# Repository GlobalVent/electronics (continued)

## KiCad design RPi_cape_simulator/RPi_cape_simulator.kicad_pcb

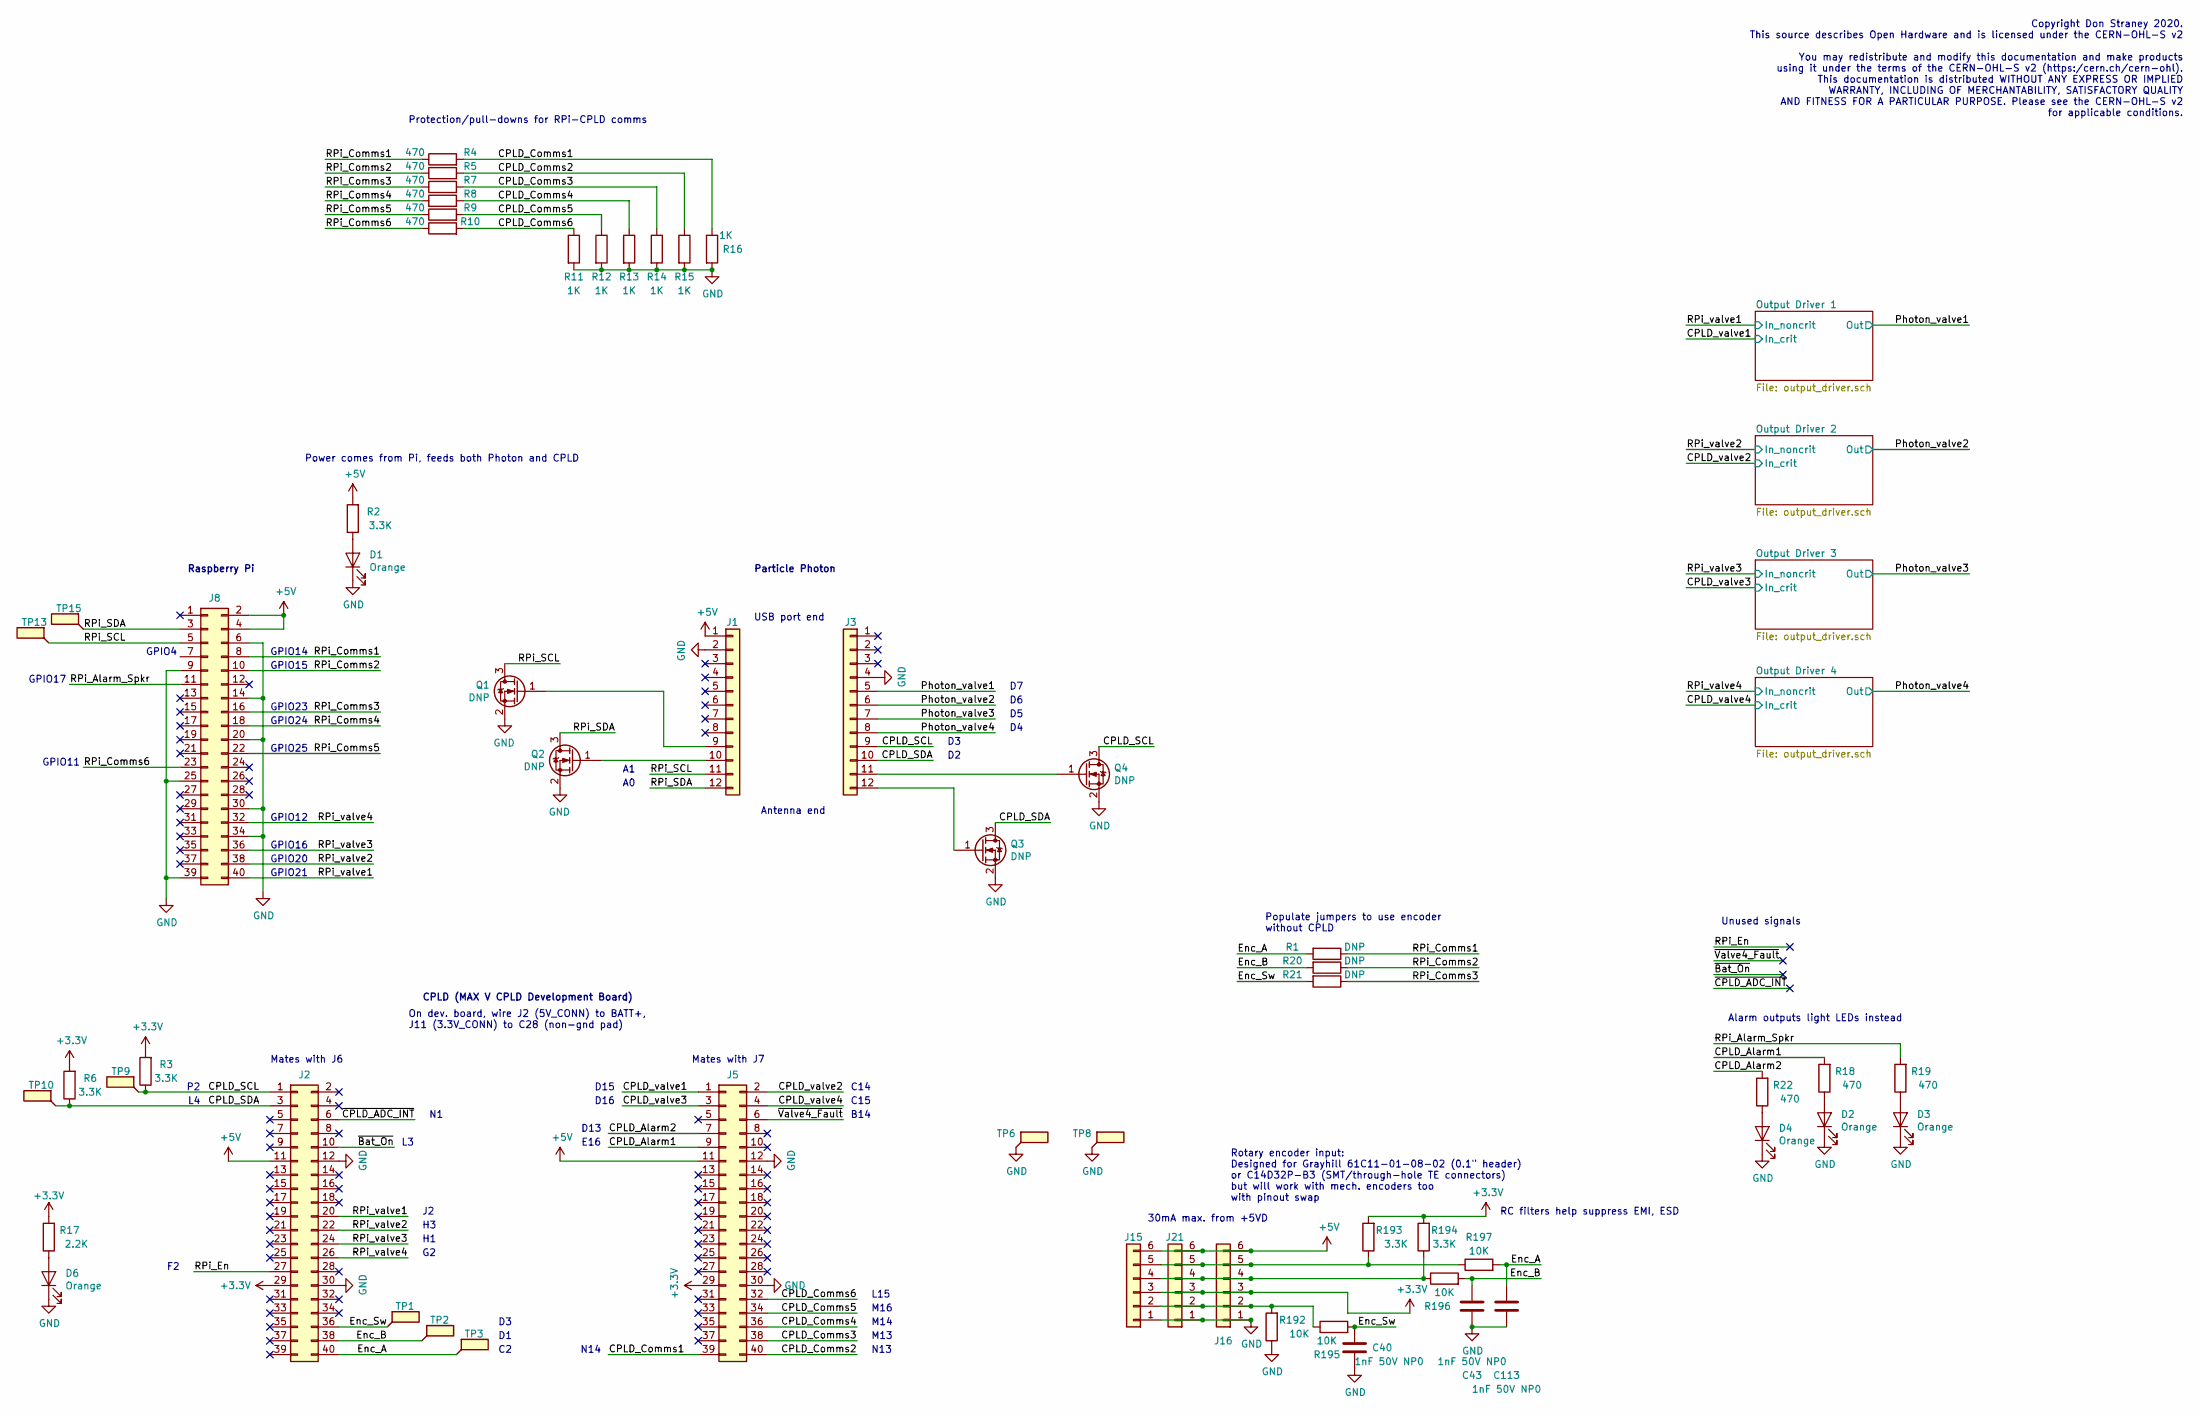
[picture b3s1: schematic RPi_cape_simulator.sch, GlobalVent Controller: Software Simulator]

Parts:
C40, C43, C113: 1nF 50V NP0; C_0603_1608Metric; Part Number 06035A102JAT2A
D1, D2, D3, D4, D6: Orange; LED_0805_2012Metric; Part Number HSMD-C170
J1, J3: Conn_01x12; PinSocket_1x12_P2.54mm_Vertical
J2, J5, J8: Conn_02x20_Odd_Even; PinSocket_2x20_P2.54mm_Vertical; Part Number PPPC202LFBN-RC
J15: Conn_01x06; TE_188275-6; Part Number 188275-6
J16: Conn_01x06; PinSocket_1x06_P2.54mm_Vertical
J21: Conn_01x06; TE_215079-6; Part Number 215079-6
Q1, Q2, Q3, Q4: DNP; SOT-23_Handsoldering
R1, R20, R21: DNP; R_0805_2012Metric
R2, R3, R6, R193, R194: 3.3K; R_0805_2012Metric
R4, R5, R7, R8, R9, R10, R18, R19, R22: 470; R_0805_2012Metric
R11, R12, R13, R14, R15, R16: 1K; R_0805_2012Metric
R17: 2.2K; R_0805_2012Metric
R192, R195, R196, R197: 10K; R_0805_2012Metric
TP1, TP2, TP3, TP6, TP8, TP9, TP10, TP13, TP15: TestPoint_Flag; TestPoint_Keystone_5019_Minature; Part Number 5019

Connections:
+3V3: J2.29, J5.29, J15.3, J16.3, J21.3, R3.2, R6.2, R17.2, R193.2, R194.2; also elsewhere on the board
+5V: J1.1, J2.11, J5.11, J8.2, J8.4, J15.6, J16.6, J21.6, R2.2
/CPLD_Alarm1: J5.9, R18.2
/CPLD_Alarm2: J5.7, R22.2
/CPLD_Comms1: J5.39, R4.2, R16.1
/CPLD_Comms2: J5.40, R5.2, R15.1
/CPLD_Comms3: J5.38, R7.2, R14.1
/CPLD_Comms4: J5.36, R8.2, R13.1
/CPLD_Comms5: J5.34, R9.2, R12.1
/CPLD_Comms6: J5.32, R10.2, R11.1
/CPLD_SCL: J2.1, J3.9, Q4.3 (D), R3.1, TP9.1
/CPLD_SDA: J2.3, J3.10, Q3.3 (D), R6.1, TP10.1
/CPLD_valve1: J5.1; also elsewhere on the board
/CPLD_valve2: J5.2; also elsewhere on the board
/CPLD_valve3: J5.3; also elsewhere on the board
/CPLD_valve4: J5.4; also elsewhere on the board
/Enc_A: C113.2, J2.40, R1.2, R197.2, TP3.1
/Enc_B: C43.2, J2.38, R20.2, R196.2, TP2.1
/Enc_Sw: C40.2, J2.36, R21.2, R195.2, TP1.1
/Photon_valve1: J3.5; also elsewhere on the board
/Photon_valve2: J3.6; also elsewhere on the board
/Photon_valve3: J3.7; also elsewhere on the board
/Photon_valve4: J3.8; also elsewhere on the board
/RPi_Alarm_Spkr: J8.11, R19.2
/RPi_Comms1: J8.8, R1.1, R4.1
/RPi_Comms2: J8.10, R5.1, R20.1
/RPi_Comms3: J8.16, R7.1, R21.1
/RPi_Comms4: J8.18, R8.1
/RPi_Comms5: J8.22, R9.1
/RPi_Comms6: J8.23, R10.1
/RPi_En: J2.27
/RPi_SCL: J1.11, J8.5, Q1.3 (D), TP13.1
/RPi_SDA: J1.12, J8.3, Q2.3 (D), TP15.1
/RPi_valve1: J2.20, J8.40; also elsewhere on the board
/RPi_valve2: J2.22, J8.38; also elsewhere on the board
/RPi_valve3: J2.24, J8.36; also elsewhere on the board
/RPi_valve4: J2.26, J8.32; also elsewhere on the board
/~Bat_On: J2.10
/~CPLD_ADC_INT: J2.6
/~Valve4_Fault: J5.6
GND: C40.1, C43.1, C113.1, D1.1 (K), D2.1 (K), D3.1 (K), D4.1 (K), D6.1 (K), J1.2, J2.12, J2.30, J3.4, J5.12, J5.30, J8.6, J8.9, J8.14, J8.20, J8.25, J8.30, J8.34, J8.39, J15.1, J16.1, J21.1, Q1.2 (S), Q2.2 (S), Q3.2 (S), Q4.2 (S), R11.2, R12.2, R13.2, R14.2, R15.2, R16.2, R192.1, TP6.1, TP8.1; also elsewhere on the board
unnamed: D1.2 (A), R2.1
unnamed: D2.2 (A), R18.1
unnamed: D3.2 (A), R19.1
unnamed: D4.2 (A), R22.1
unnamed: D6.2 (A), R17.1
unnamed: J1.9, Q1.1 (G)
unnamed: J1.10, Q2.1 (G)
unnamed: J3.11, Q4.1 (G)
unnamed: J3.12, Q3.1 (G)
unnamed: J15.2, J16.2, J21.2, R192.2, R195.1
unnamed: J15.4, J16.4, J21.4, R194.1, R196.1
unnamed: J15.5, J16.5, J21.5, R193.1, R197.1

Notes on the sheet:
GPIO17
GPIO24
GPIO23
GPIO25
GPIO11
Rotary encoder input: Designed for Grayhill 61C11-01-08-02 (0.1" header) or C14D32P-B3 (SMT/through-hole TE connectors) but will work with mech. encoders too with pinout swap
GPIO16
GPIO20
GPIO21
RC filters help suppress EMI, ESD
30mA max. from +5VD
GPIO12
GPIO14
GPIO15
CPLD (MAX V CPLD Development Board)
Mates with J6
Mates with J7
On dev. board, wire J2 (5V_CONN) to BATT+, J11 (3.3V_CONN) to C28 (non-gnd pad)
B14
E16
Copyright Don Straney 2020. This source describes Open Hardware and is licensed under the CERN-OHL-S v2 You may redistribute and modify this documentation and make products using it under the terms of the CERN-OHL-S v2 (https:/cern.ch/cern-ohl). This documentation is distributed WITHOUT ANY EXPRESS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
GPIO4
Raspberry Pi
Particle Photon
USB port end
Antenna end
Power comes from Pi, feeds both Photon and CPLD
Unused signals
Alarm outputs light LEDs instead
Protection/pull-downs for RPi-CPLD comms
L15
M16
M14
M13
N13
N14
D15
C14
D16
C15

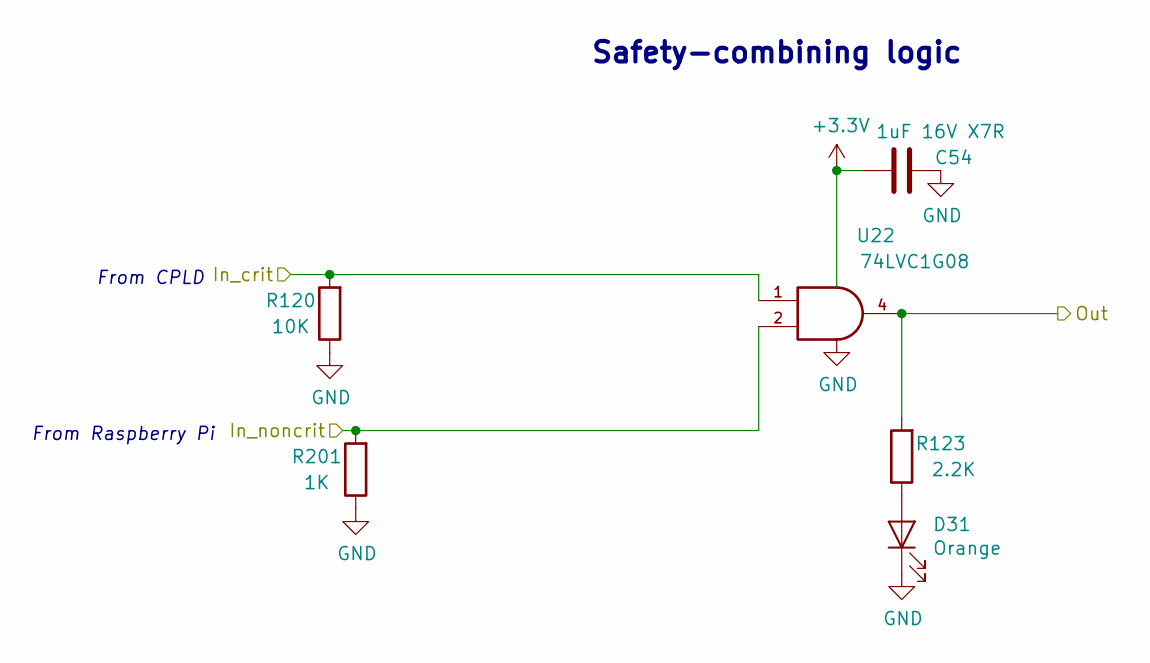
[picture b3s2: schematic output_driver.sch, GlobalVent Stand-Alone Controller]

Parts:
C28: 1uF 16V X7R; C_0805_2012Metric; Part Number C0805C105K4RACTU
D12: Orange; LED_0805_2012Metric; Part Number HSMD-C170
R53: 10K; R_0805_2012Metric
R56: 2.2K; R_0805_2012Metric
R198: 1K; R_0805_2012Metric
U8: 74LVC1G08; SOT-23-5; Part Number SN74LVC1G08DBVR

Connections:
+3V3: C28.2, U8.5 (VCC); also elsewhere on the board
/CPLD_valve1: R53.2, U8.1; also elsewhere on the board
/Photon_valve1: R56.2, U8.4; also elsewhere on the board
/RPi_valve1: R198.2, U8.2; also elsewhere on the board
GND: C28.1, D12.1 (K), R53.1, R198.1, U8.3 (GND); also elsewhere on the board
unnamed: D12.2 (A), R56.1

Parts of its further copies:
C48, C51, C54: 1uF 16V X7R; C_0805_2012Metric; Part Number C0805C105K4RACTU
D21, D26, D31: Orange; LED_0805_2012Metric; Part Number HSMD-C170
R106, R113, R120: 10K; R_0805_2012Metric
R109, R116, R123: 2.2K; R_0805_2012Metric
R199, R200, R201: 1K; R_0805_2012Metric
U18, U20, U22: 74LVC1G08; SOT-23-5; Part Number SN74LVC1G08DBVR

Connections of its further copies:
+3V3: C48.2, C51.2, C54.2, U18.5 (VCC), U20.5 (VCC), U22.5 (VCC); also elsewhere on the board
/CPLD_valve2: R106.2, U18.1; also elsewhere on the board
/CPLD_valve3: R113.2, U20.1; also elsewhere on the board
/CPLD_valve4: R120.2, U22.1; also elsewhere on the board
/Photon_valve2: R109.2, U18.4; also elsewhere on the board
/Photon_valve3: R116.2, U20.4; also elsewhere on the board
/Photon_valve4: R123.2, U22.4; also elsewhere on the board
/RPi_valve2: R199.2, U18.2; also elsewhere on the board
/RPi_valve3: R200.2, U20.2; also elsewhere on the board
/RPi_valve4: R201.2, U22.2; also elsewhere on the board
GND: C48.1, C51.1, C54.1, D21.1 (K), D26.1 (K), D31.1 (K), R106.1, R113.1, R120.1, R199.1, R200.1, R201.1, U18.3 (GND), U20.3 (GND), U22.3 (GND); also elsewhere on the board
unnamed: D21.2 (A), R109.1
unnamed: D26.2 (A), R116.1
unnamed: D31.2 (A), R123.1

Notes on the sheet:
From Raspberry Pi
From CPLD
Safety-combining logic

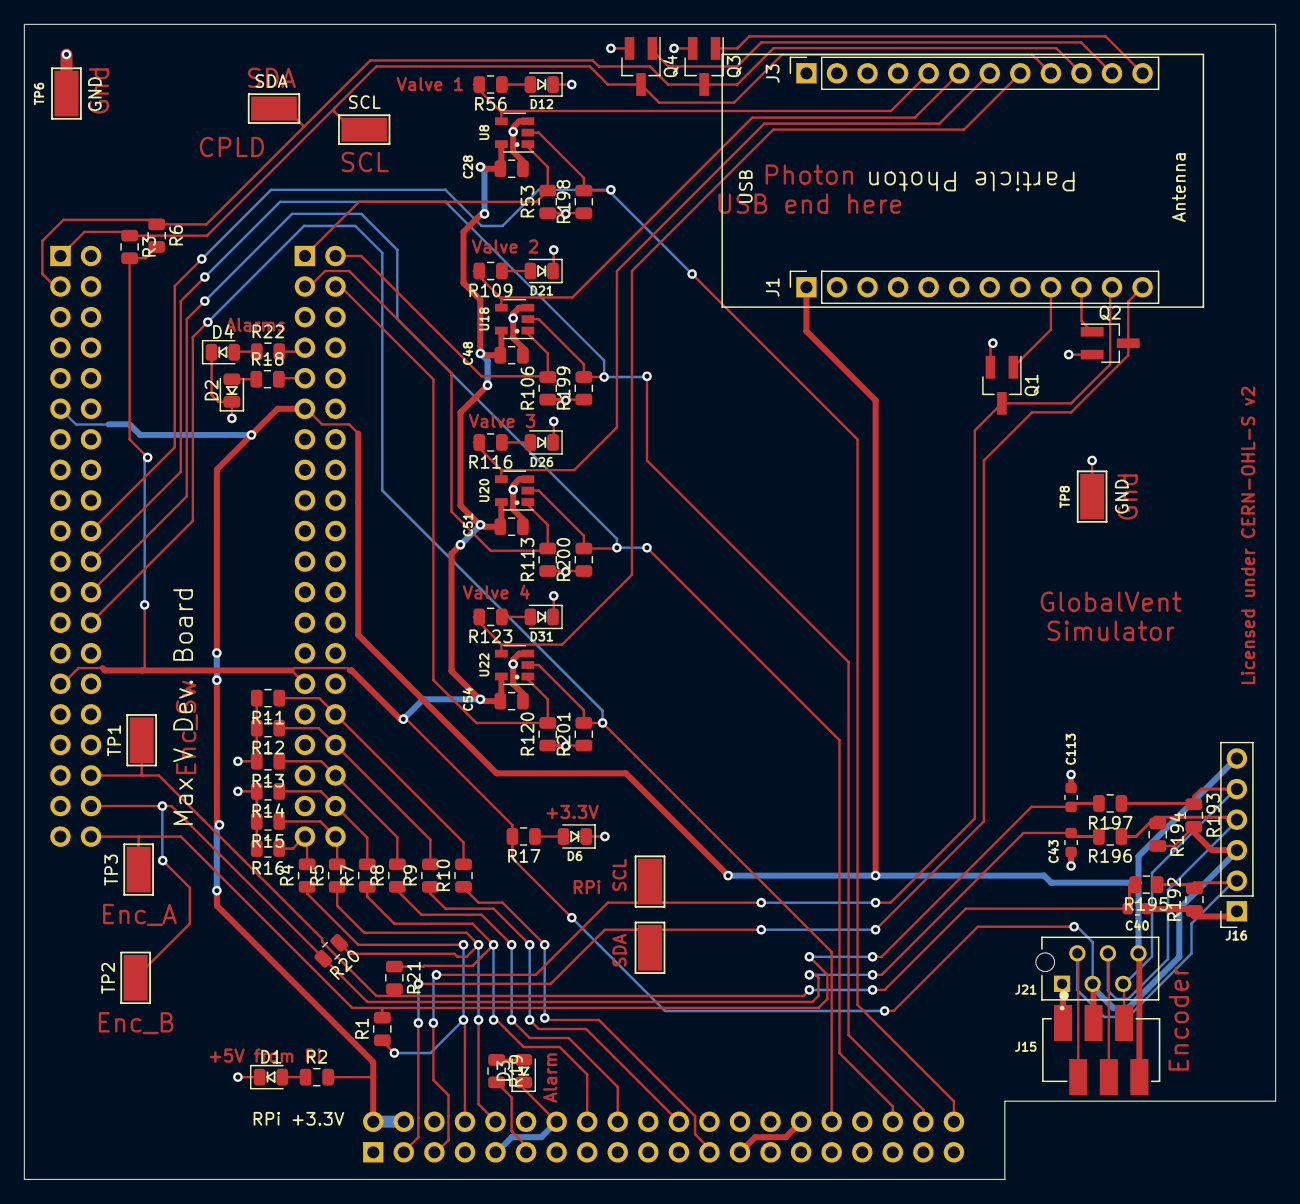
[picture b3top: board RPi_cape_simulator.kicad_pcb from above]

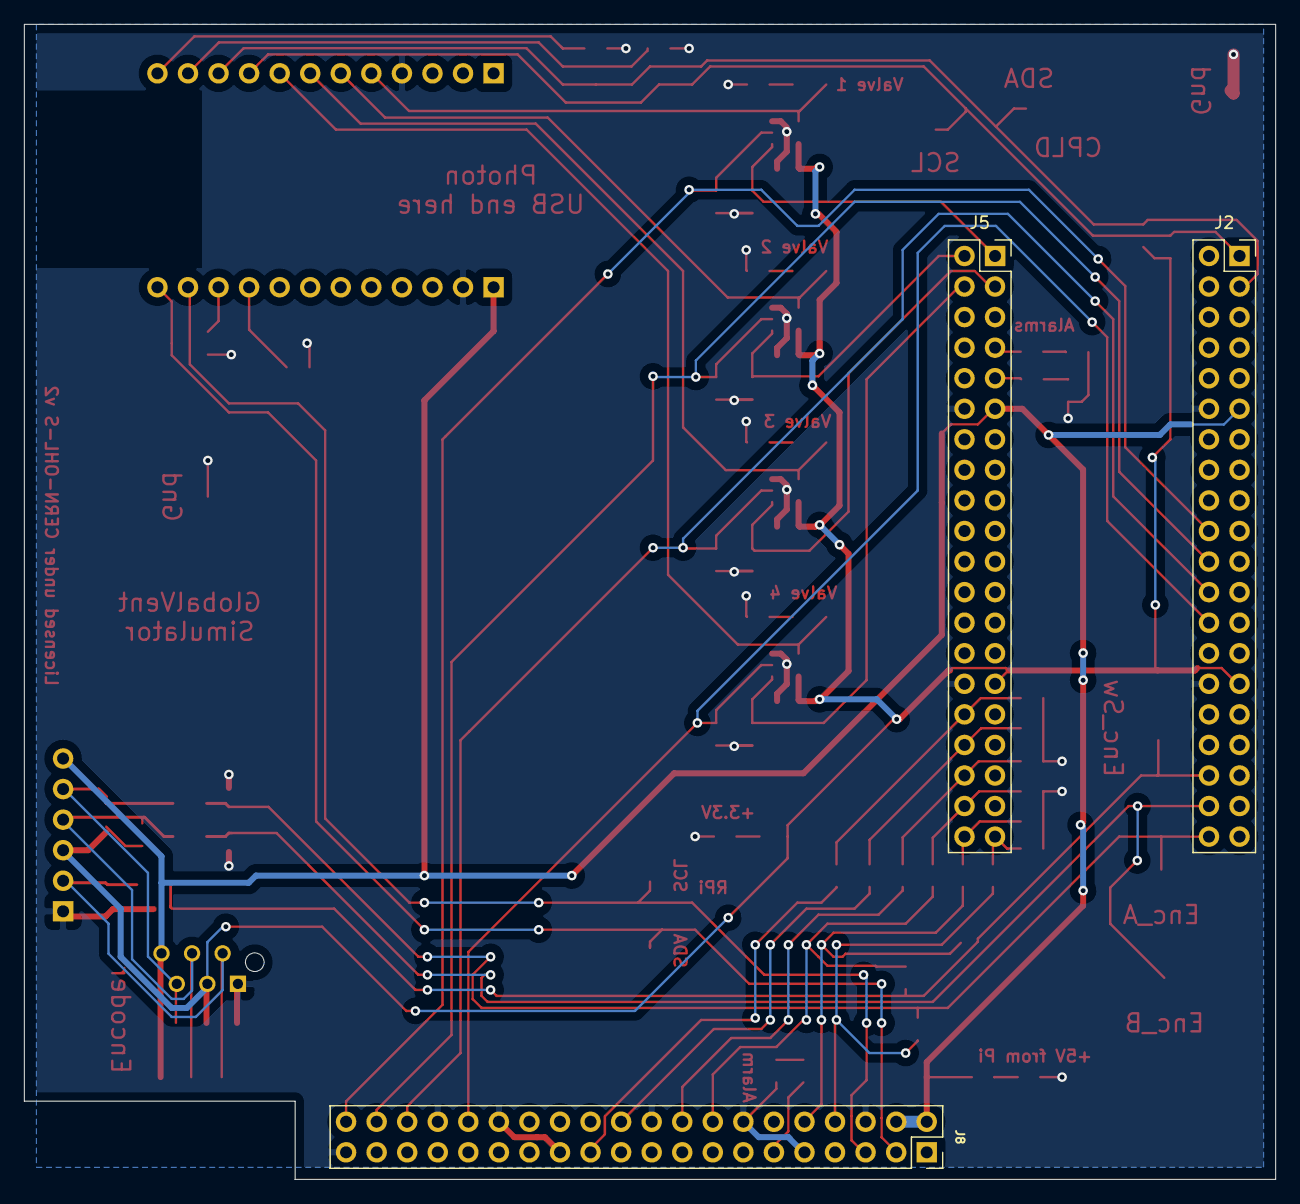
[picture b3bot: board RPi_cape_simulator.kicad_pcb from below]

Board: 2 copper layers, 104.0 x 96.0 mm, 81 parts (3 on the bottom side), 53 nets.

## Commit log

2020-04-08 Initial creation
2020-04-08 Extra info, post-design-review fixes
    Added extra info on existing alternate circuit options
    Added extra info on parts selection
    Created initial PCB file
    Added bulk cap to +5V input
    Design review fixes:
    Moved Raspberry Pi PWM output to GPIO18 to take advantage of hardware PWM
2020-04-08 Cleanup
2020-04-10 Finished schematic, most of PCB placement
    Added error budget for analog inputs
    Finished most of PCB placement and started routing
    Added R185, R186 to allow powering CPLD from alarm power for better power-down alarm sound flexibility
    Changed power-down alarm monitoring from +5VD to +3.3V, and put +5VA and +24VA monitoring as DNP by default, to match the CPLD's ability to run off backup battery and monitor +5VA/+24VA
    Moved from 3x AA (4.5V) to 4x AA (6V) alarm battery for better audio voltage, and added PNP diode-ORing circuit (Q12 etc.) to accomodate higher voltage, changed low-battery threshold to 5V
    Added pull-down resistors to sensor op-amp outputs to help extend low-end output range
2020-04-12 Finished layout, minor design changes
    Assigned CPLD pins
    Finished routing PCB
    Moved rotary encoder inputs to CPLD
    Removed separate decoupling caps for smaller CPLD footprint due to routing constraints
    Added pull-downs on CPLD inputs for each valve driver (R198 etc.)
2020-04-13 Digital pressure sensors
    Added two digital pressure sensors each, on Raspberry Pi and CPLD I2C busses; preliminary layout only until mechanical details are finalized
    Added gnd plane on bottom layer for heatsinking 5V regulators
2020-04-16 Better valve monitoring, finalized layout and manufacturing files
    Created assembly and fabrication drawings, assigned all BOM parts, generally made design ready for ordering
    Added strain-relief slots and barb mounting dimensions for digital pressure sensors
    Changed valve drivers from discrete power MOSFETs to "smart" industrial/automotive driver ICs for the current monitoring, including valve-movement monitor for #4
    Connected RPi_Valve* signals to larger CPLD footprint, changed Raspberry Pi pin assignment as a result to ease PCB routing
    Updated footprints, page layout to create readable assembly drawing
    Added current-measurement testpoints for CPLD power from BATT+
2020-04-17 Manufacturing clean-up
    Corrections and additions to BOM etc. for manufacturing
    Added power draw tracking spreadsheet
2020-04-18 Cleanup
    Consolidated gitignore
    Removed remaining backup file from repo
2020-04-19 Better docs, failure mode/protection summary
    Created list of protection features / failure modes + function bring-up plan
    Added more alternate parts for Pi connector
    Added candidate parts for other headers, fans, and speakers
2020-04-19 Failure mode clarification
    Clarified indirect ability to sense low 24V input by observing valve currents lower than expected/nominal
2020-04-19 Added missing cases
    Added missing "short on downstream analog" rails cases, where +5VA or sensor-+24VA shorts would trip fuses without triggering noticeable upstream faults
2020-04-19 Failure mode corrections
2020-04-19 Safety additions
    Switched CPLD_ADC7 to +24V monitoring (from +5V monitoring), and added CPLD ~Bat_On digital input(s) to know when it's running from backup battery, to cover low-input-voltage edge cases
    Added series 1K resistors (R226-231) on CPLD<->RPi Comms1-6 lines, to protect CPLD in case of overvoltage from RPi failure
    Added optional input TVS D23 to handle sustained over-voltage or large surges
2020-04-19 Cleanup, docs
2020-04-19 Docs cleanup
2020-04-20 +5VA outage detection
    Separated +1.8V and +5VA monitoring and added +3.3V output for +5VA on ~5VA_On signal to CPLD, to cover an extra failure mode
2020-04-21 Documentation updates
    Changed organization to "US JamVent Team" on all drawings
    Put BOM in better format for picky automated-BOM scripts (Sierra Circuits) that can't handle space or newline separators in refdes list
    Marked TE pressure sensors as DNP on BOM, for manual soldering to avoid damage from cleaning and automated processes
    Adjusted bom.ini to leave out the pressure-sensor-barb fittings (mechanical only)
2020-04-22 "Final" manufacturing zip file
    Fixed previous forgetfullness in adding updated fab/assembly drawings and BOM to "final" manufacturing zip file
2020-04-22 Zip cleanup
    Removed costing BOM accidentally added to zip file
2020-04-22 Footprint corrections, software docs
    Added pinout and I2C description for software devs
    Changed erroneously-"through hole"-marked SnapEDA footprints to SMT, so no longer missing from pick-and-place centroid file
2020-04-24 Analog upgrades and extra encoder connectors
    Renamed a few files
    Removed "costing BOM" as difficult to keep up to date, easy to regenerate
    Toughened under-voltage detect circuits by adding hysteresis to +5V detect for +BATT diode-OR (R236), filtering to power-down alarm detect input (C85)
    Added connector options (J15, J21) for Grayhill C14-series rotary encoder with cable
    Changed R190 from 3K to 2.4K to increase overhead on base current required for saturation, and consolidate BOM
    Added 3 solderable testpoints for expanding CPLD pin options (TP44-46), adjusted some CPLD pin assignments to allow physical routing to pins
2020-04-28 Added Pin spreadsheet with simulation info
2020-05-13 Initial add of "Quick and Dirty Prototype" 2-layer
2020-05-13 Fixed BOM
    Added missing dual-diode part number
2020-05-13 Updates based on testing, extra documentation
    Added thermal calculations, possible thermal-induced problems to fault-condition list
    Renamed error calculations file
    Added some bringup tests
    Changed 24V LED resistors (R20, R22) to 24.9K to consolidate BOM
    Adjusted audio amp volume and filtering according to breadboard experiments
    Moved bottom-end mounting holes and encoder connectors to avoid interfering mechanically with Raspberry Pi
2020-05-13 Input ORing-diode details
    Changed part number and improved heatsinking for input power OR-ing diode
2020-05-14 Cleanup, manufacturing
    Added doc on differences between 'proto' version and 'full' version
    Added manufacturing README in proto version
    Removed unused hardwired-limited O2 alarm nets in proto version
    Fixed missed-annotation on D1 in full version
2020-05-27 Admin (naming, license), improvements based on testing
    Updated name on schematic, PCB silkscreen
    Added 3 mounting holes on inside area of board for better mechanical robustness
    Removed extra unused pressure sensor barb packages from library
    Fixed Phoenix spring connector footprints, and added 3D models from Phoenix website
    Added 3D models to TE encoder connector footprints, QFP-100 for CPLD, and 5019 testpoint
    Changed DIAG_EN pin connection from valve drivers from +24V (too high) to +3.3V
2020-05-27 Admin (licensing, naming)
    Put under CERN open hardware license
    Changed name to GlobalVent
2020-06-07 Created simulator board
    Created simulator board to connect Pi, CPLD dev board, and Photon-as-software-simulator
2020-06-07 Cache updates
2020-06-12 Misc small updates
    Updated non-precision op-amp list to work with valve-motion-detect circuit's peak detector (needs low bias current)
    Created 3D model for "quick and dirty" prototype board
    Added rework on simulator for Photon pinout
2020-07-05 Design update based on changed software/firmware/pneumatics reqs
    Swapped Max V CPLD for Max 10 FPGA
    Removed +1.8V regulator and monitoring (in power-down alarm) because Max 10 FPGA has internal regulator
    Changed FPGA's valve-enable pull-downs from 1K to 10K because Max 10 floats the outputs during power-up/programming (instead of Max V's internal pull-ups)
    Changed low-pressure sensor from BMP388 to MS5607 for more manufacturable footprint / high availability, and moved all digital pressure sensors to daughterboard for repairability
    Changed single op-amps in analog pressure sensor inputs / valve motion detect circuits to TLV6001 for better bias current, correct footprint
    Removed excessive DNP
2020-07-05 Initial
    Created separate pressure sensor daughterboard
2020-07-05 Removed 3d component models
2020-07-05 Created/updated manufacturing files
    Created new manufacturing files for pressure sensor daughterboard
    Updated stats w/corrected numbers (based on extra counts for non-plated holes, vias in mounting hole rings) for main board
    Created schematic PDF for pressure sensor daughterboard
    Updated schematic version for pressure sensor daughterboard
2020-07-06 3D updates
    Removed extra files that shouldn't be in repo
    Associated QFP footprint with 3D model
2020-08-31 3D models, parts
    Added 3D model for LMZ14203
    Added parts options for daughterboard connection
2020-09-01 Added add'l parts selection lists
    Added FPGA, CPU, display selection lists
